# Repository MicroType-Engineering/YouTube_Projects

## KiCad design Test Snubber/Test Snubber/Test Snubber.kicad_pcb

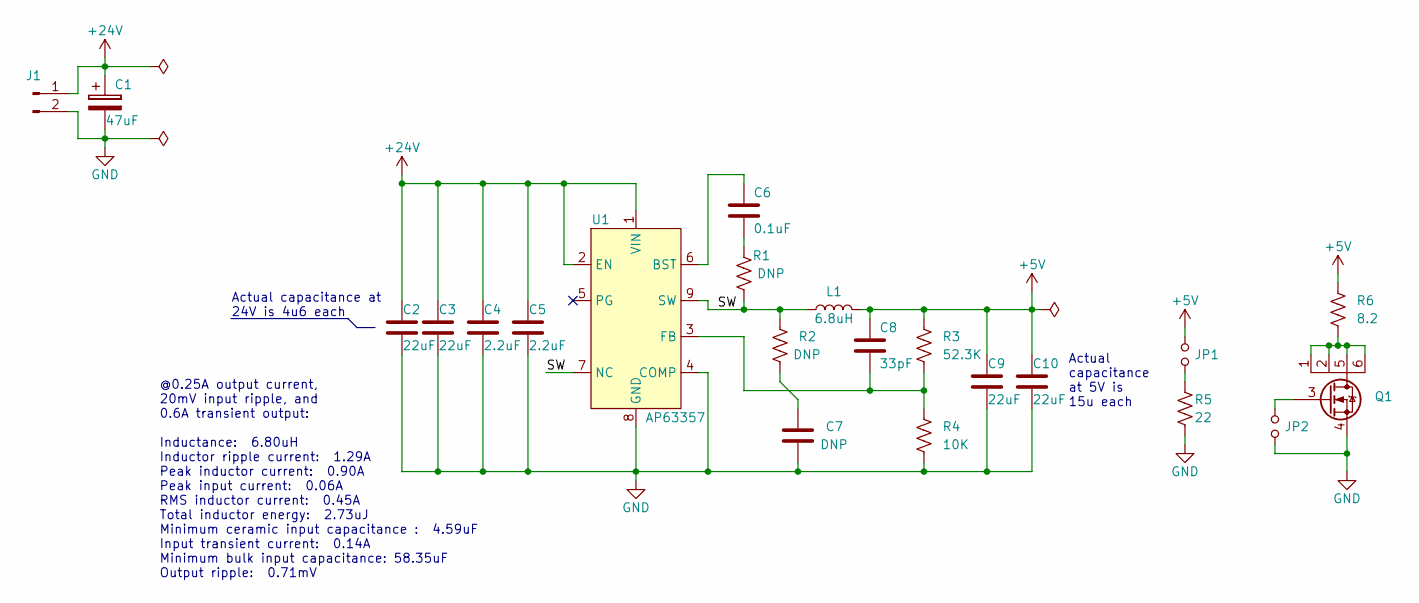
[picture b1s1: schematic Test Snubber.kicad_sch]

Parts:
C1: EEE-1VA470WP; CAPAE660X580L260X65N
C2, C3, C9, C10: GRM32ER71E226ME15L; CAPACITOR_1210N
C4, C5: GRM188R61H225ME11D; CAPACITOR_0603N
C6: CC0603KRX7R9BB104; CAPACITOR_0603N
C7: DNP; CAPACITOR_0603N
C8: CC0603JRNPO9BN330; CAPACITOR_0603N
J1: 1702473
JP1, JP2: Jumper_NO_Small; PinHeader_1x02_P2.54mm_Vertical
L1: 74438336068; INDUCTOR_3030N
Q1: SI1442DH-T1-GE3; SOT23-6P95_285X140L45X42N
R1, R2: DNP; RESISTOR_0603N
R3: RC0603FR-0752K3L; RESISTOR_0603N
R4: RC0603JR-0710KL; RESISTOR_0603N
R5: 350222RJT; RESISTOR_2010N
R6: 35028R2JT; RESISTOR_2010N
U1: AP63357QZV-7

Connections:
+5V: C8.1, C9.1, C10.1, JP1.2, L1.2, R3.1, R6.1
+24V: C1.1, C2.1, C3.1, C4.1, C5.1, J1.1, U1.1 (VIN), U1.2 (EN)
/SW: L1.1, R1.1, R2.1, U1.7 (NC), U1.9 (SW)
GND: C1.2, C2.2, C3.2, C4.2, C5.2, C7.2, C9.2, C10.2, J1.2, JP2.1, Q1.4 (S), R4.2, R5.2, U1.4 (COMP), U1.8 (GND)
unnamed: C6.1, U1.6 (BST)
unnamed: C6.2, R1.2
unnamed: C7.1, R2.2
unnamed: C8.2, R3.2, R4.1, U1.3 (FB)
unnamed: JP1.1, R5.1
unnamed: JP2.2, Q1.3 (G)
unnamed: Q1.1 (D), Q1.2 (D), Q1.5 (D), Q1.6 (D), R6.2

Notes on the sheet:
Actual capacitance at 5V is 15u each
@0.25A output current, 20mV input ripple, and 0.6A transient output: Inductance: 6.80uH Inductor ripple current: 1.29A Peak inductor current: 0.90A Peak input current: 0.06A RMS inductor current: 0.45A Total inductor energy: 2.73uJ Minimum ceramic input capacitance : 4.59uF Input transient current: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
Actual capacitance at 24V is 4u6 each

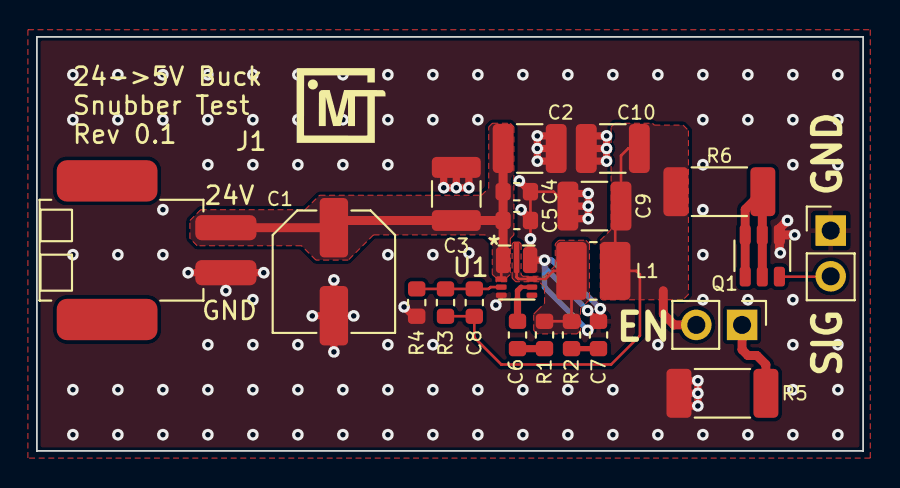
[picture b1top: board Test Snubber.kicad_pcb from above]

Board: 2 copper layers, 45.9 x 23.0 mm, 22 parts (0 on the bottom side), 11 nets.

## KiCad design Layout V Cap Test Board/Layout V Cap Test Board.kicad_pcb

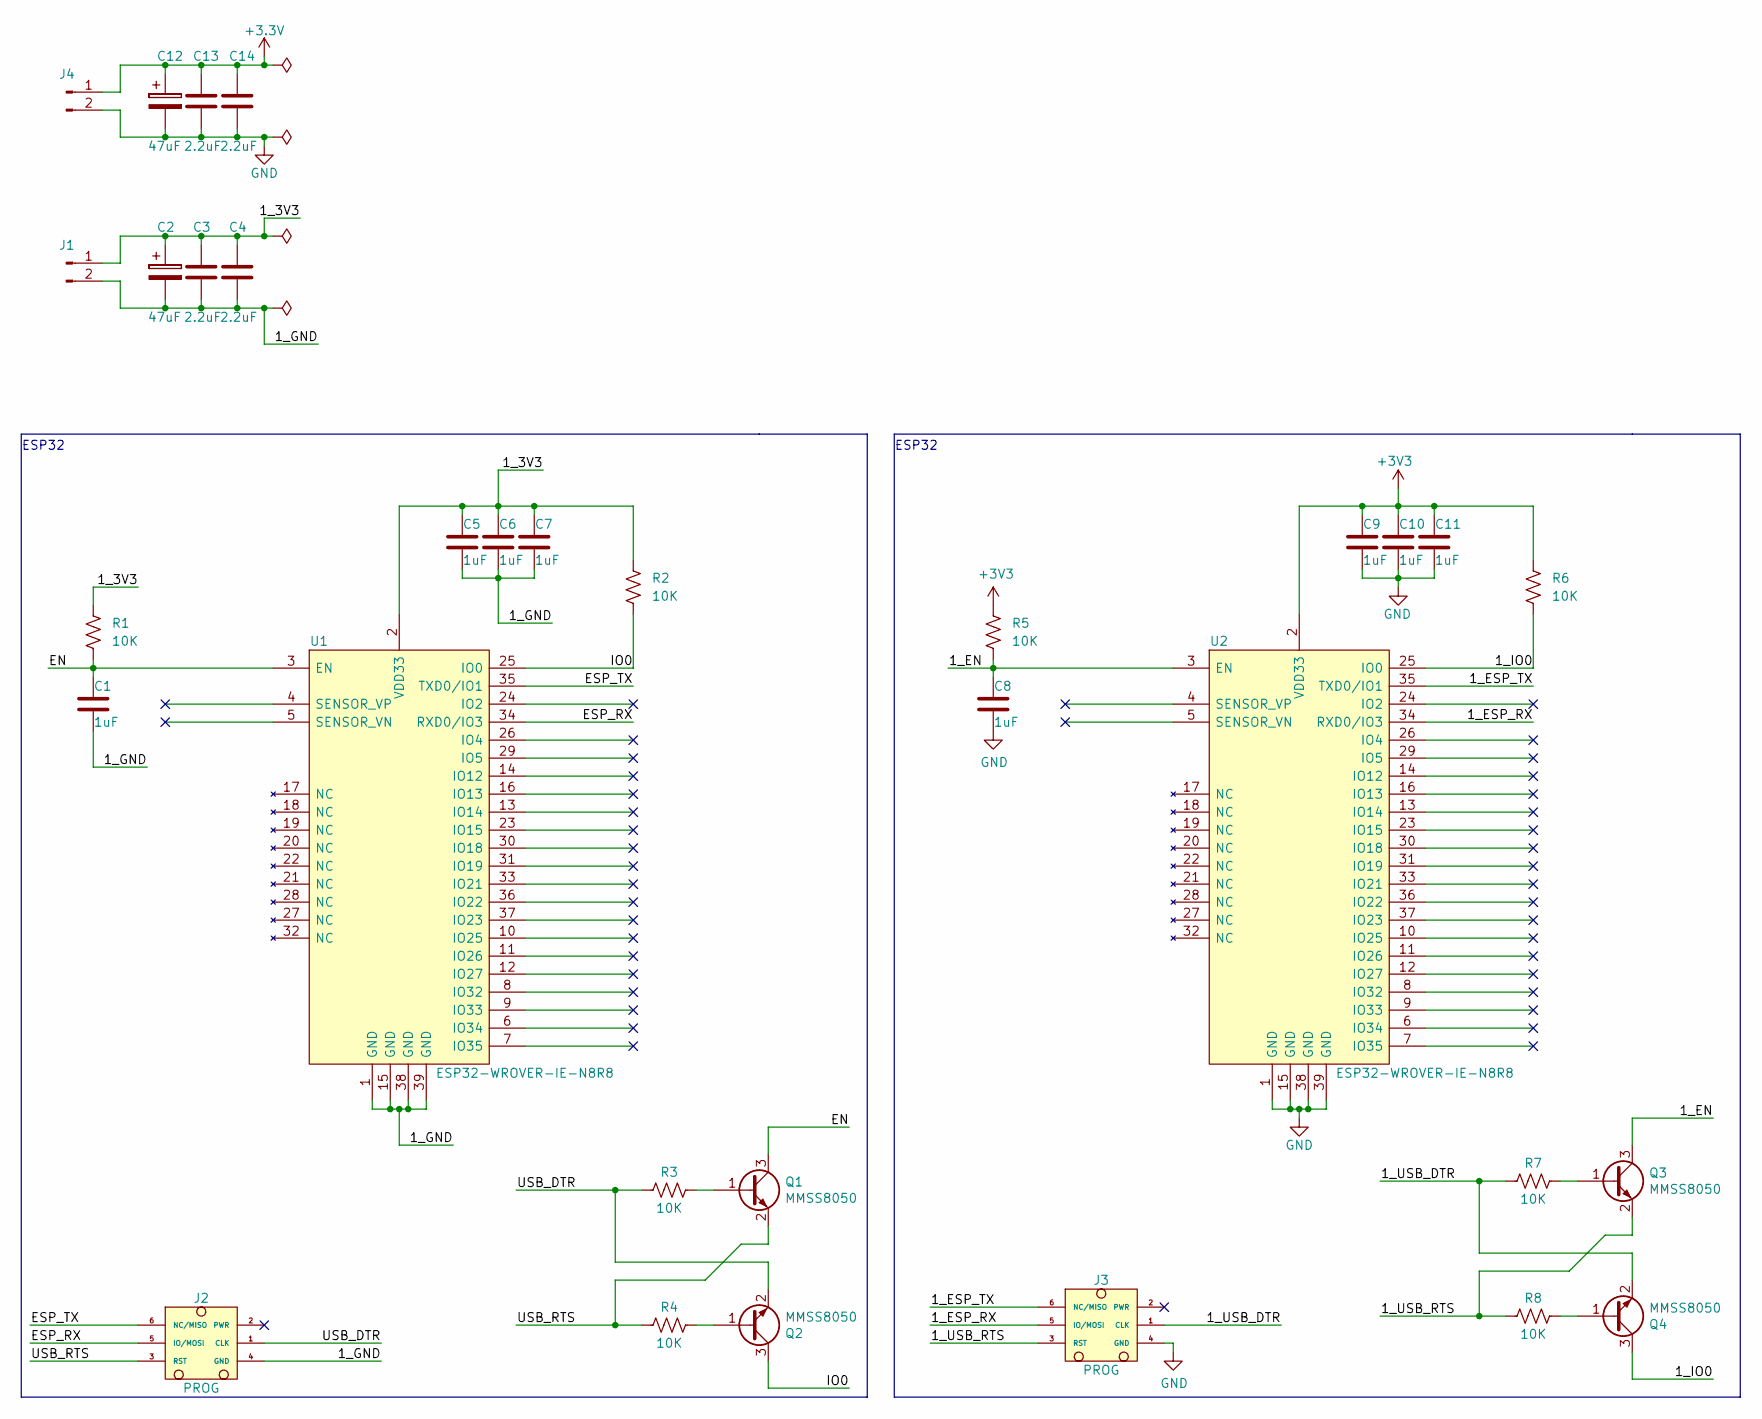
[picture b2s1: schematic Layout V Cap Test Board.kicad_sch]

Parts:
C1, C5, C6, C7, C8, C9, C10, C11: CC0603KRX5R9BB105; CAPACITOR_0603N
C2, C12: EMVE160ADA470MF55G; CAPAE660X550D720L265X65N
C3, C4, C13, C14: EMK107BB7225MA-T; RESISTOR_0603N
J1, J4: 1702473
J2, J3: Tag_Connect_Programmer_6-Pin; TC2030_SMALL
Q1, Q2, Q3, Q4: MMSS8050-L-TP; MMSS8050-L-TPN
R1, R2, R3, R4, R5, R6, R7, R8: RC0603JR-0710KL; RESISTOR_0603N
U1, U2: ESP32-WROVER-IE-N8R8; ESP32-WROVER-IE-N8R8_EXT_ANT

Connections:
/1_3V3: C2.1, C3.1, C4.1, C5.1, C6.1, C7.1, J1.1, R1.1, R2.1, U1.2 (VDD33)
/1_EN: C8.1, Q3.3 (C), R5.2, U2.3 (EN)
/1_ESP_RX: J3.5 (IO/MOSI), U2.34 (RXD0/IO3)
/1_ESP_TX: J3.6 (NC/MISO), U2.35 (TXD0/IO1)
/1_GND: C1.2, C2.2, C3.2, C4.2, C5.2, C6.2, C7.2, J1.2, J2.4 (GND), U1.1 (GND), U1.15 (GND), U1.38 (GND), U1.39 (GND)
/1_IO0: Q4.3 (C), R6.2, U2.25 (IO0)
/1_USB_DTR: J3.1 (CLK), Q4.2 (E), R7.1
/1_USB_RTS: J3.3 (RST), Q3.2 (E), R8.1
/EN: C1.1, Q1.3 (C), R1.2, U1.3 (EN)
/ESP_RX: J2.5 (IO/MOSI), U1.34 (RXD0/IO3)
/ESP_TX: J2.6 (NC/MISO), U1.35 (TXD0/IO1)
/IO0: Q2.3 (C), R2.2, U1.25 (IO0)
/USB_DTR: J2.1 (CLK), Q2.2 (E), R3.1
/USB_RTS: J2.3 (RST), Q1.2 (E), R4.1
GND: C8.2, C9.2, C10.2, C11.2, C12.2, C13.2, C14.2, J3.4 (GND), J4.2, U2.1 (GND), U2.15 (GND), U2.38 (GND), U2.39 (GND)
unnamed: Q1.1 (B), R3.2
unnamed: Q2.1 (B), R4.2
unnamed: Q3.1 (B), R7.2
unnamed: Q4.1 (B), R8.2

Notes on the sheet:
ESP32

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
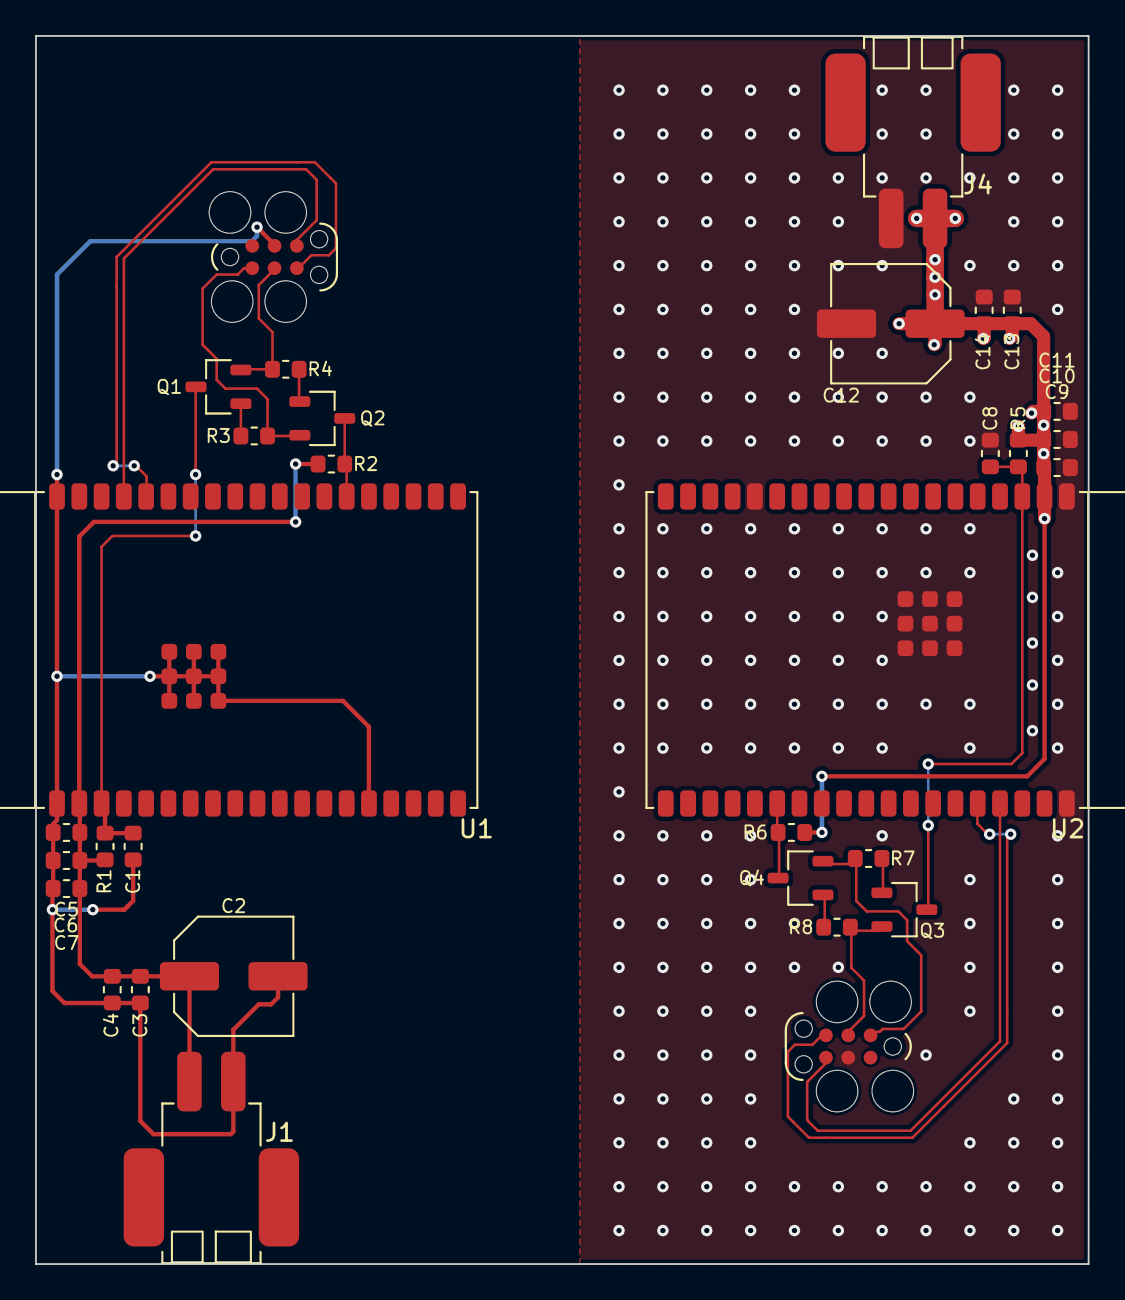
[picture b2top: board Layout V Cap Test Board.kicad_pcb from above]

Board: 4 copper layers, 60.0 x 70.0 mm, 32 parts (0 on the bottom side), 20 nets.

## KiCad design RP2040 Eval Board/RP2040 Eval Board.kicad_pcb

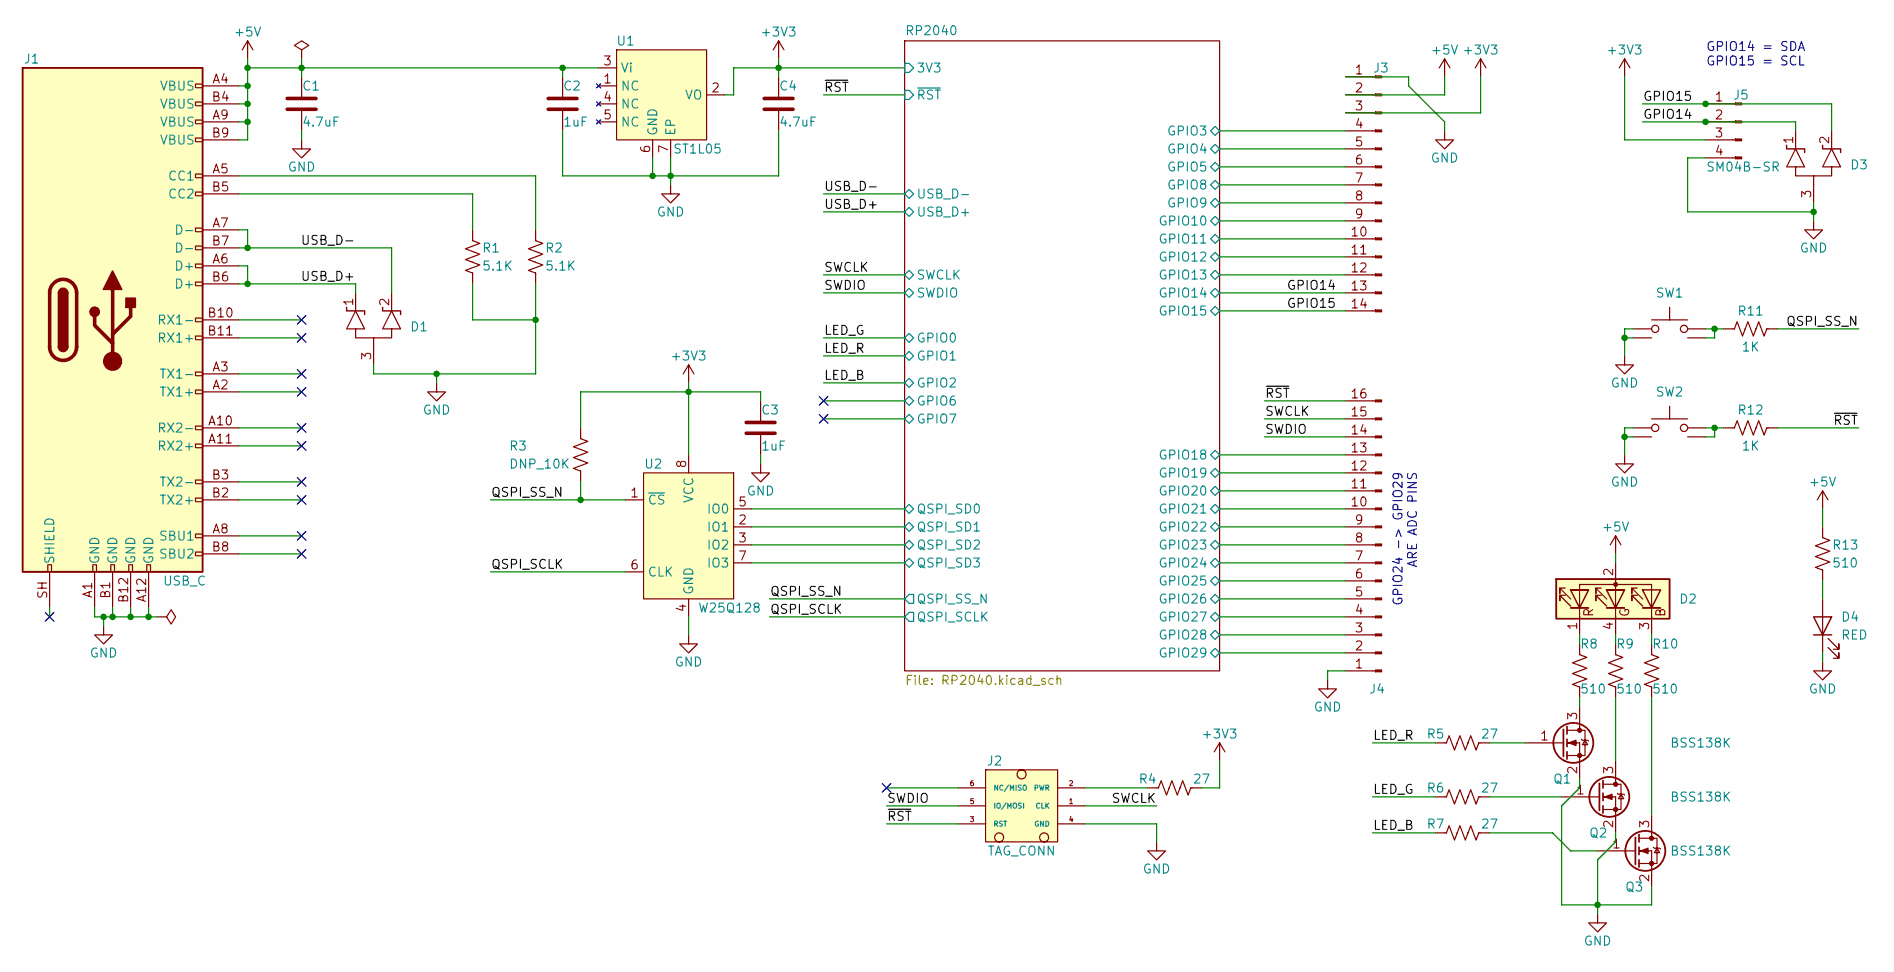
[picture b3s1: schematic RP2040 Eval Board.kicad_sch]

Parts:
C1, C4: GRM21BR61H475KE51L; CAPACITOR_0805N
C2, C3: CC0402KRX5R7BB105; CAPACITOR_0402N
D1, D3: ESD7L5.0DT5G; DIOSOFL3P40_120X120X55L29X21N
D2: CLVBA-FKA-CAEDH8BBB7A363; CLVBA-FKA-CAEDH8BBB7A363N
D4: 150120RS75000; LED_1206N
J1: 12401598E4#2A
J2: Tag_Connect_Programmer_6-Pin; TC2030_SMALL_NO_LEGS
J3: _GENERIC_CONNECTOR_01x14; PinHeader_1x14_P2.54mm_Vertical
J4: _GENERIC_CONNECTOR_01x16; PinHeader_1x16_P2.54mm_Vertical
J5: SM04B-SRSS-TB(LF)(SN)
Q1, Q2, Q3: BSS138K; SOT23-3P95_285X115L45X42N
R1, R2: RC0402JR-075K1L; RESISTOR_0402N
R3: DNP; RESISTOR_0402N
R4, R5, R6, R7: RC0402FR-0727RL; RESISTOR_0402N
R8, R9, R10, R13: RC0402JR-07510RL; RESISTOR_0402N
R11, R12: RC0402JR-071KL; RESISTOR_0402N
SW1, SW2: PTS_647_SN38_SMTR2_LFS; PTS_647_SN70_SMTR2_LFS
U1: ST1L05APU33R; SON7P95_300X300X100L40X34T236X162N
U2: W25Q128JVSIM_TR; SOIC8P127_528X790X216L65X41N

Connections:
+3V3: C3.1, C4.1, J3.3, J5.3, R3.1, R4.2, U1.2 (VO), U2.8 (VCC); also elsewhere on the board
+5V: C1.1, C2.1, D2.2 (A), J1.A4 (VBUS), J1.A9 (VBUS), J1.B4 (VBUS), J1.B9 (VBUS), J3.2, R13.1, U1.3 (Vi)
/GPIO14: D3.1 (A1), J3.13, J5.2; also elsewhere on the board
/GPIO15: D3.2 (A2), J3.14, J5.1; also elsewhere on the board
/LED_B: R7.1; also elsewhere on the board
/LED_G: R6.1; also elsewhere on the board
/LED_R: R5.1; also elsewhere on the board
/QSPI_SCLK: U2.6 (CLK); also elsewhere on the board
/QSPI_SS_N: R3.2, R11.2, U2.1 (~CS); also elsewhere on the board
/RP2040/GPIO3: J3.4; also elsewhere on the board
/RP2040/GPIO4: J3.5; also elsewhere on the board
/RP2040/GPIO5: J3.6; also elsewhere on the board
/RP2040/GPIO8: J3.7; also elsewhere on the board
/RP2040/GPIO9: J3.8; also elsewhere on the board
/RP2040/GPIO10: J3.9; also elsewhere on the board
/RP2040/GPIO11: J3.10; also elsewhere on the board
/RP2040/GPIO12: J3.11; also elsewhere on the board
/RP2040/GPIO13: J3.12; also elsewhere on the board
/RP2040/GPIO18: J4.13; also elsewhere on the board
/RP2040/GPIO19: J4.12; also elsewhere on the board
/RP2040/GPIO20: J4.11; also elsewhere on the board
/RP2040/GPIO21: J4.10; also elsewhere on the board
/RP2040/GPIO22: J4.9; also elsewhere on the board
/RP2040/GPIO23: J4.8; also elsewhere on the board
/RP2040/GPIO24: J4.7; also elsewhere on the board
/RP2040/GPIO25: J4.6; also elsewhere on the board
/RP2040/GPIO26: J4.5; also elsewhere on the board
/RP2040/GPIO27: J4.4; also elsewhere on the board
/RP2040/GPIO28: J4.3; also elsewhere on the board
/RP2040/GPIO29: J4.2; also elsewhere on the board
/RP2040/QSPI_SD0: U2.5 (IO0); also elsewhere on the board
/RP2040/QSPI_SD1: U2.2 (IO1); also elsewhere on the board
/RP2040/QSPI_SD2: U2.3 (IO2); also elsewhere on the board
/RP2040/QSPI_SD3: U2.7 (IO3); also elsewhere on the board
/SWCLK: J2.1 (CLK), J4.15; also elsewhere on the board
/SWDIO: J2.5 (IO/MOSI), J4.14; also elsewhere on the board
/USB_D+: D1.1 (A1), J1.A6 (D+), J1.B6 (D+); also elsewhere on the board
/USB_D-: D1.2 (A2), J1.A7 (D-), J1.B7 (D-); also elsewhere on the board
/~RST: J2.3 (RST), J4.16, R12.2; also elsewhere on the board
GND: C1.2, C2.2, C3.2, C4.2, D1.3 (common), D3.3 (common), D4.C, J1.A1 (GND), J1.A12 (GND), J1.B1 (GND), J1.B12 (GND), J2.4 (GND), J3.1, J4.1, J5.4, Q1.2 (S), Q2.2 (S), Q3.2 (S), R1.2, R2.2, SW1.1, SW1.2, SW2.1, SW2.2, U1.6 (GND), U1.7 (EP), U2.4 (GND); also elsewhere on the board
unnamed: D2.1 (RC), R8.1
unnamed: D2.3 (BC), R10.1
unnamed: D2.4 (GC), R9.1
unnamed: D4.A, R13.2
unnamed: J1.A5 (CC1), R2.1
unnamed: J1.B5 (CC2), R1.1
unnamed: J2.2 (PWR), R4.1
unnamed: Q1.1 (G), R5.2
unnamed: Q1.3 (D), R8.2
unnamed: Q2.1 (G), R6.2
unnamed: Q2.3 (D), R9.2
unnamed: Q3.1 (G), R7.2
unnamed: Q3.3 (D), R10.2
unnamed: R11.1, SW1.3, SW1.4
unnamed: R12.1, SW2.3, SW2.4

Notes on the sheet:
GPIO24 -> GPIO29 ARE ADC PINS
GPIO14 = SDA GPIO15 = SCL

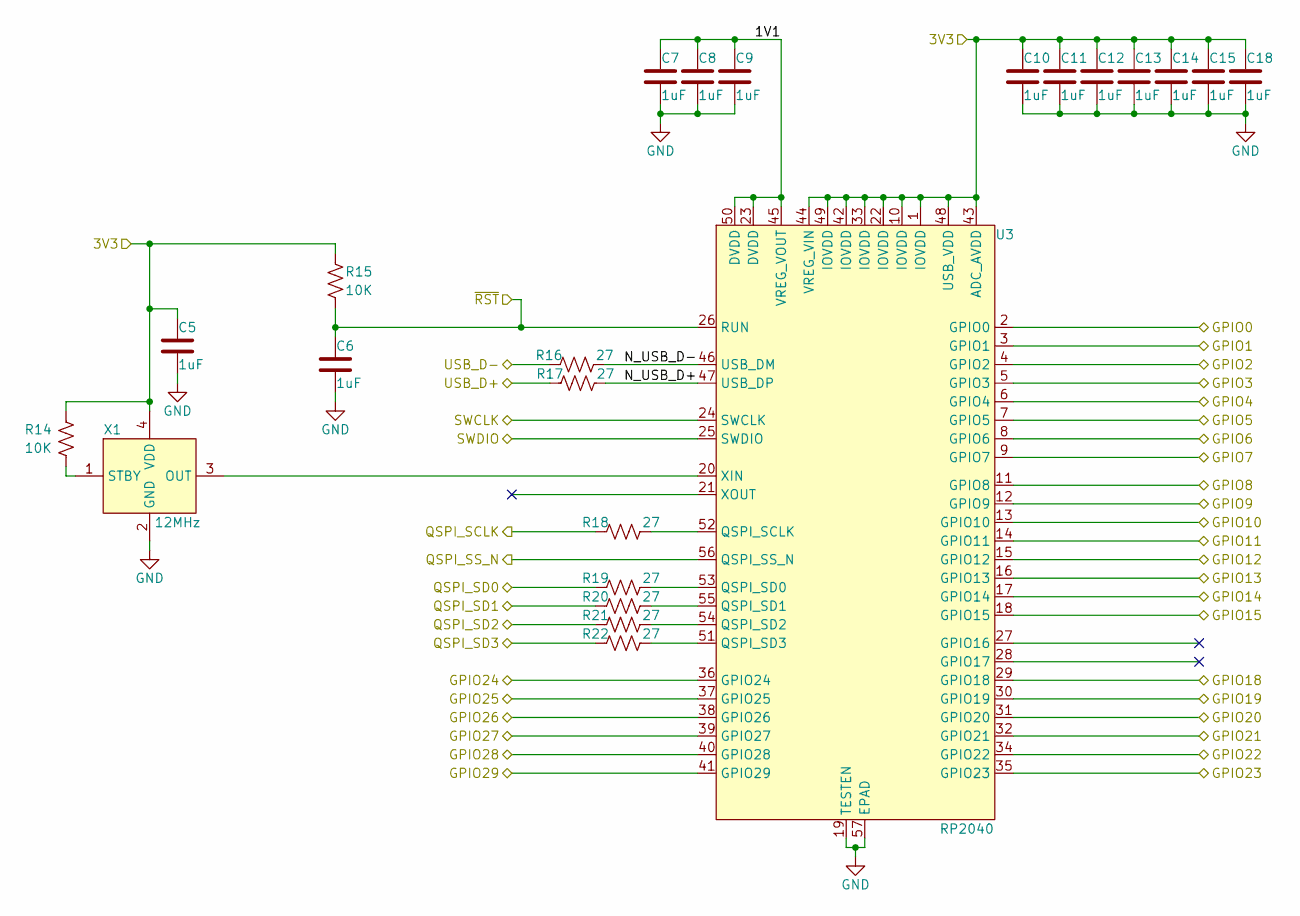
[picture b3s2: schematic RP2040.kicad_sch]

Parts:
C5, C6, C7, C8, C9, C10, C11, C12, C13, C14, C15, C18: CC0402KRX5R7BB105; CAPACITOR_0402N
R14, R15: RC0402JR-0710KL; RESISTOR_0402N
R16, R17, R18, R19, R20, R21, R22: RC0402FR-0727RL; RESISTOR_0402N
U3: RP2040; QFN57P40_700X700X90L40X18T310N
X1: ASE-12.000MHZ-ET; OSCSC4P210_320X250X120L65X90N

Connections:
+3V3: C5.1, C10.1, C11.1, C12.1, C13.1, C14.1, C15.1, C18.1, R14.2, R15.1, U3.1 (IOVDD), U3.10 (IOVDD), U3.22 (IOVDD), U3.33 (IOVDD), U3.42 (IOVDD), U3.43 (ADC_AVDD), U3.44 (VREG_VIN), U3.48 (USB_VDD), U3.49 (IOVDD), X1.4 (VDD); also elsewhere on the board
/GPIO14: U3.17 (GPIO14); also elsewhere on the board
/GPIO15: U3.18 (GPIO15); also elsewhere on the board
/LED_B: U3.4 (GPIO2); also elsewhere on the board
/LED_G: U3.2 (GPIO0); also elsewhere on the board
/LED_R: U3.3 (GPIO1); also elsewhere on the board
/QSPI_SCLK: R18.1; also elsewhere on the board
/QSPI_SS_N: U3.56 (QSPI_SS_N); also elsewhere on the board
/RP2040/1V1: C7.1, C8.1, C9.1, U3.23 (DVDD), U3.45 (VREG_VOUT), U3.50 (DVDD)
/RP2040/GPIO3: U3.5 (GPIO3); also elsewhere on the board
/RP2040/GPIO4: U3.6 (GPIO4); also elsewhere on the board
/RP2040/GPIO5: U3.7 (GPIO5); also elsewhere on the board
/RP2040/GPIO6: U3.8 (GPIO6)
/RP2040/GPIO7: U3.9 (GPIO7)
/RP2040/GPIO8: U3.11 (GPIO8); also elsewhere on the board
/RP2040/GPIO9: U3.12 (GPIO9); also elsewhere on the board
/RP2040/GPIO10: U3.13 (GPIO10); also elsewhere on the board
/RP2040/GPIO11: U3.14 (GPIO11); also elsewhere on the board
/RP2040/GPIO12: U3.15 (GPIO12); also elsewhere on the board
/RP2040/GPIO13: U3.16 (GPIO13); also elsewhere on the board
/RP2040/GPIO18: U3.29 (GPIO18); also elsewhere on the board
/RP2040/GPIO19: U3.30 (GPIO19); also elsewhere on the board
/RP2040/GPIO20: U3.31 (GPIO20); also elsewhere on the board
/RP2040/GPIO21: U3.32 (GPIO21); also elsewhere on the board
/RP2040/GPIO22: U3.34 (GPIO22); also elsewhere on the board
/RP2040/GPIO23: U3.35 (GPIO23); also elsewhere on the board
/RP2040/GPIO24: U3.36 (GPIO24); also elsewhere on the board
/RP2040/GPIO25: U3.37 (GPIO25); also elsewhere on the board
/RP2040/GPIO26: U3.38 (GPIO26); also elsewhere on the board
/RP2040/GPIO27: U3.39 (GPIO27); also elsewhere on the board
/RP2040/GPIO28: U3.40 (GPIO28); also elsewhere on the board
/RP2040/GPIO29: U3.41 (GPIO29); also elsewhere on the board
/RP2040/N_USB_D+: R17.2, U3.47 (USB_DP)
/RP2040/N_USB_D-: R16.2, U3.46 (USB_DM)
/RP2040/QSPI_SD0: R19.1; also elsewhere on the board
/RP2040/QSPI_SD1: R20.1; also elsewhere on the board
/RP2040/QSPI_SD2: R21.1; also elsewhere on the board
/RP2040/QSPI_SD3: R22.1; also elsewhere on the board
/SWCLK: U3.24 (SWCLK); also elsewhere on the board
/SWDIO: U3.25 (SWDIO); also elsewhere on the board
/USB_D+: R17.1; also elsewhere on the board
/USB_D-: R16.1; also elsewhere on the board
/~RST: C6.1, R15.2, U3.26 (RUN); also elsewhere on the board
GND: C5.2, C6.2, C7.2, C8.2, C9.2, C10.2, C11.2, C12.2, C13.2, C14.2, C15.2, C18.2, U3.19 (TESTEN), U3.57 (EPAD), X1.2 (GND); also elsewhere on the board
unnamed: R14.1, X1.1 (STBY)
unnamed: R18.2, U3.52 (QSPI_SCLK)
unnamed: R19.2, U3.53 (QSPI_SD0)
unnamed: R20.2, U3.55 (QSPI_SD1)
unnamed: R21.2, U3.54 (QSPI_SD2)
unnamed: R22.2, U3.51 (QSPI_SD3)
unnamed: U3.20 (XIN), X1.3 (OUT)

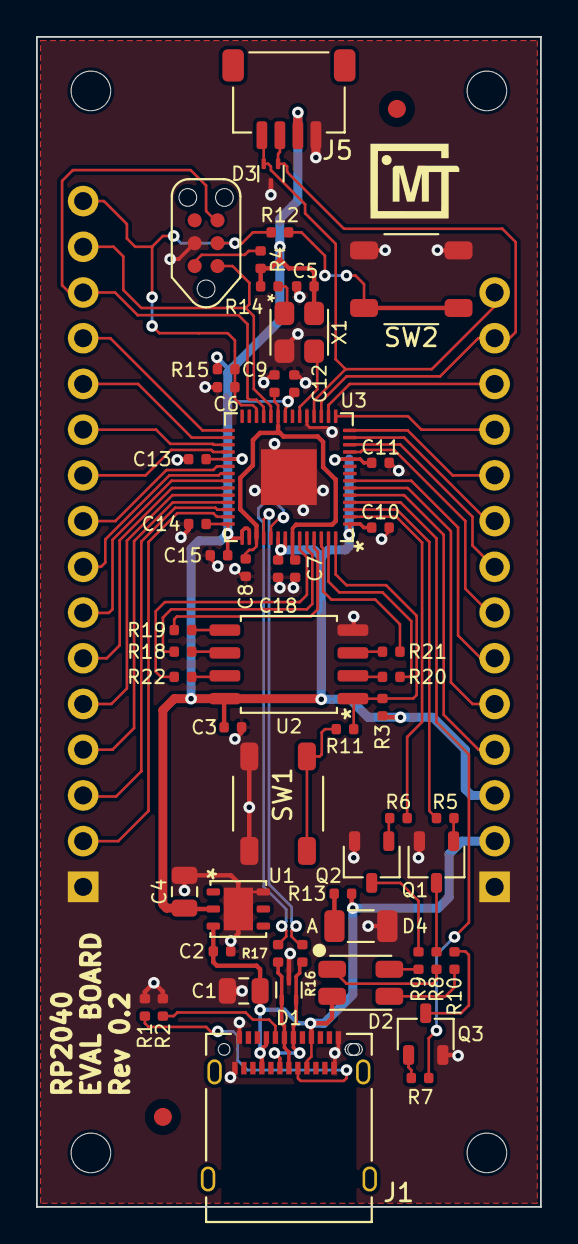
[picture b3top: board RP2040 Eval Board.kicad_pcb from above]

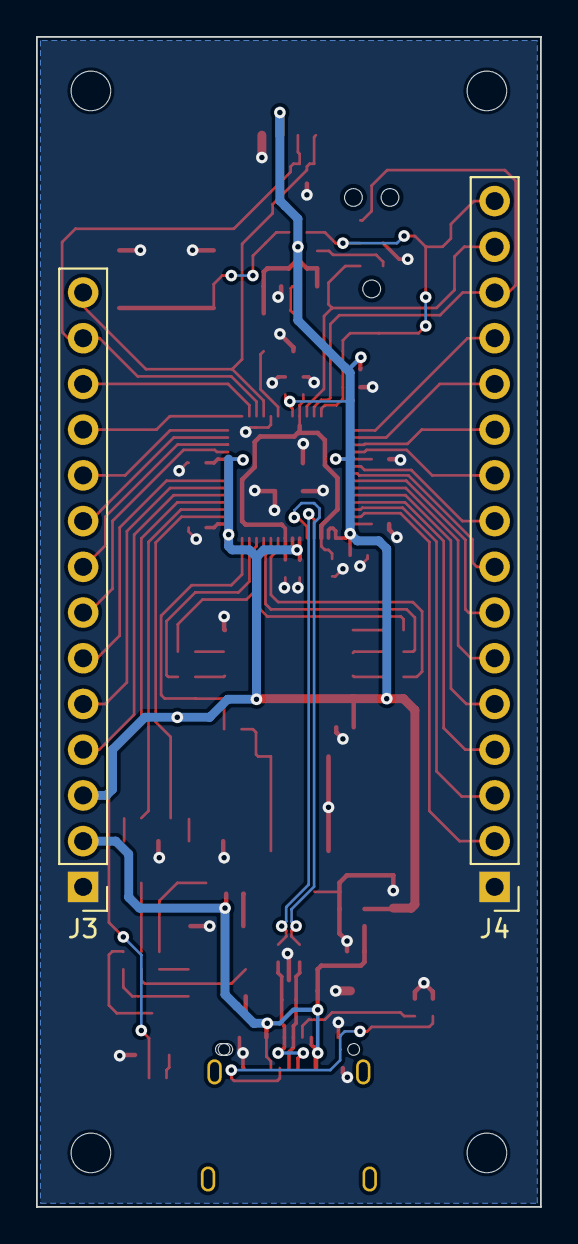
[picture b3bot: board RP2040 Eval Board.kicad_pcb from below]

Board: 4 copper layers, 28.0 x 65.0 mm, 56 parts (2 on the bottom side), 65 nets.

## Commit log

2022-12-23 Adds RP2040 eval board and the Test Snubber Projects
2022-12-24 Finishes Layout V Cap Test Board
2022-12-24 Finishes Test Snubber board
2022-12-28 Increases snubber panel size for PCBWay
